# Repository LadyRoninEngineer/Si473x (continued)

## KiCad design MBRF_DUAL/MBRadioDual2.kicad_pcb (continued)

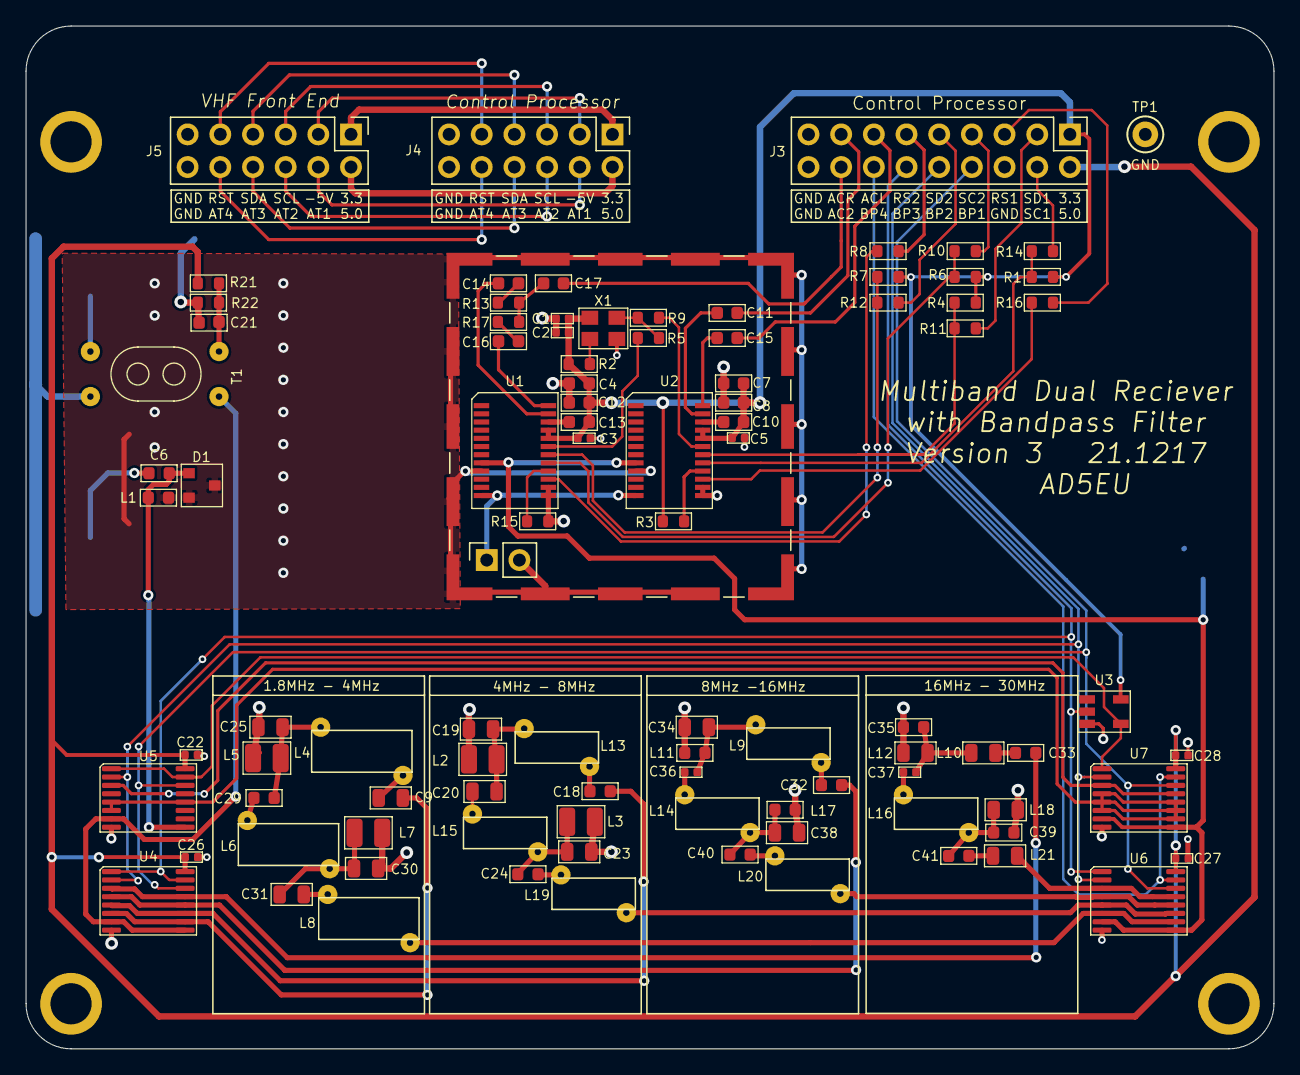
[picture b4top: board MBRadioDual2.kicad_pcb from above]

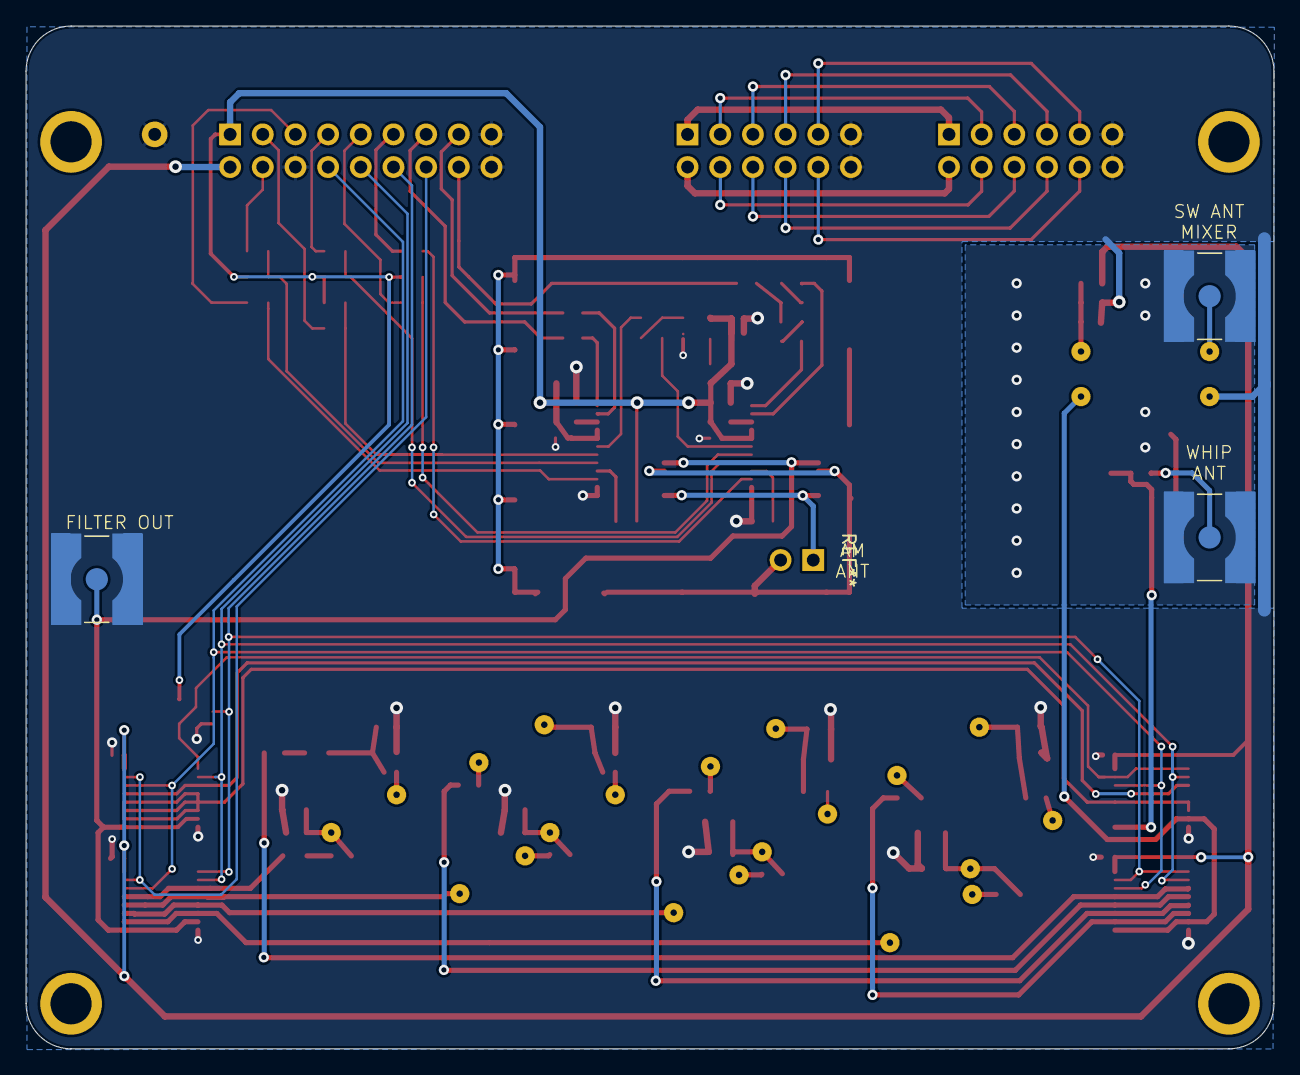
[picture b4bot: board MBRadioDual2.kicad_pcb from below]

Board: 2 copper layers, 97.0 x 79.5 mm, 99 parts (3 on the bottom side), 86 nets.

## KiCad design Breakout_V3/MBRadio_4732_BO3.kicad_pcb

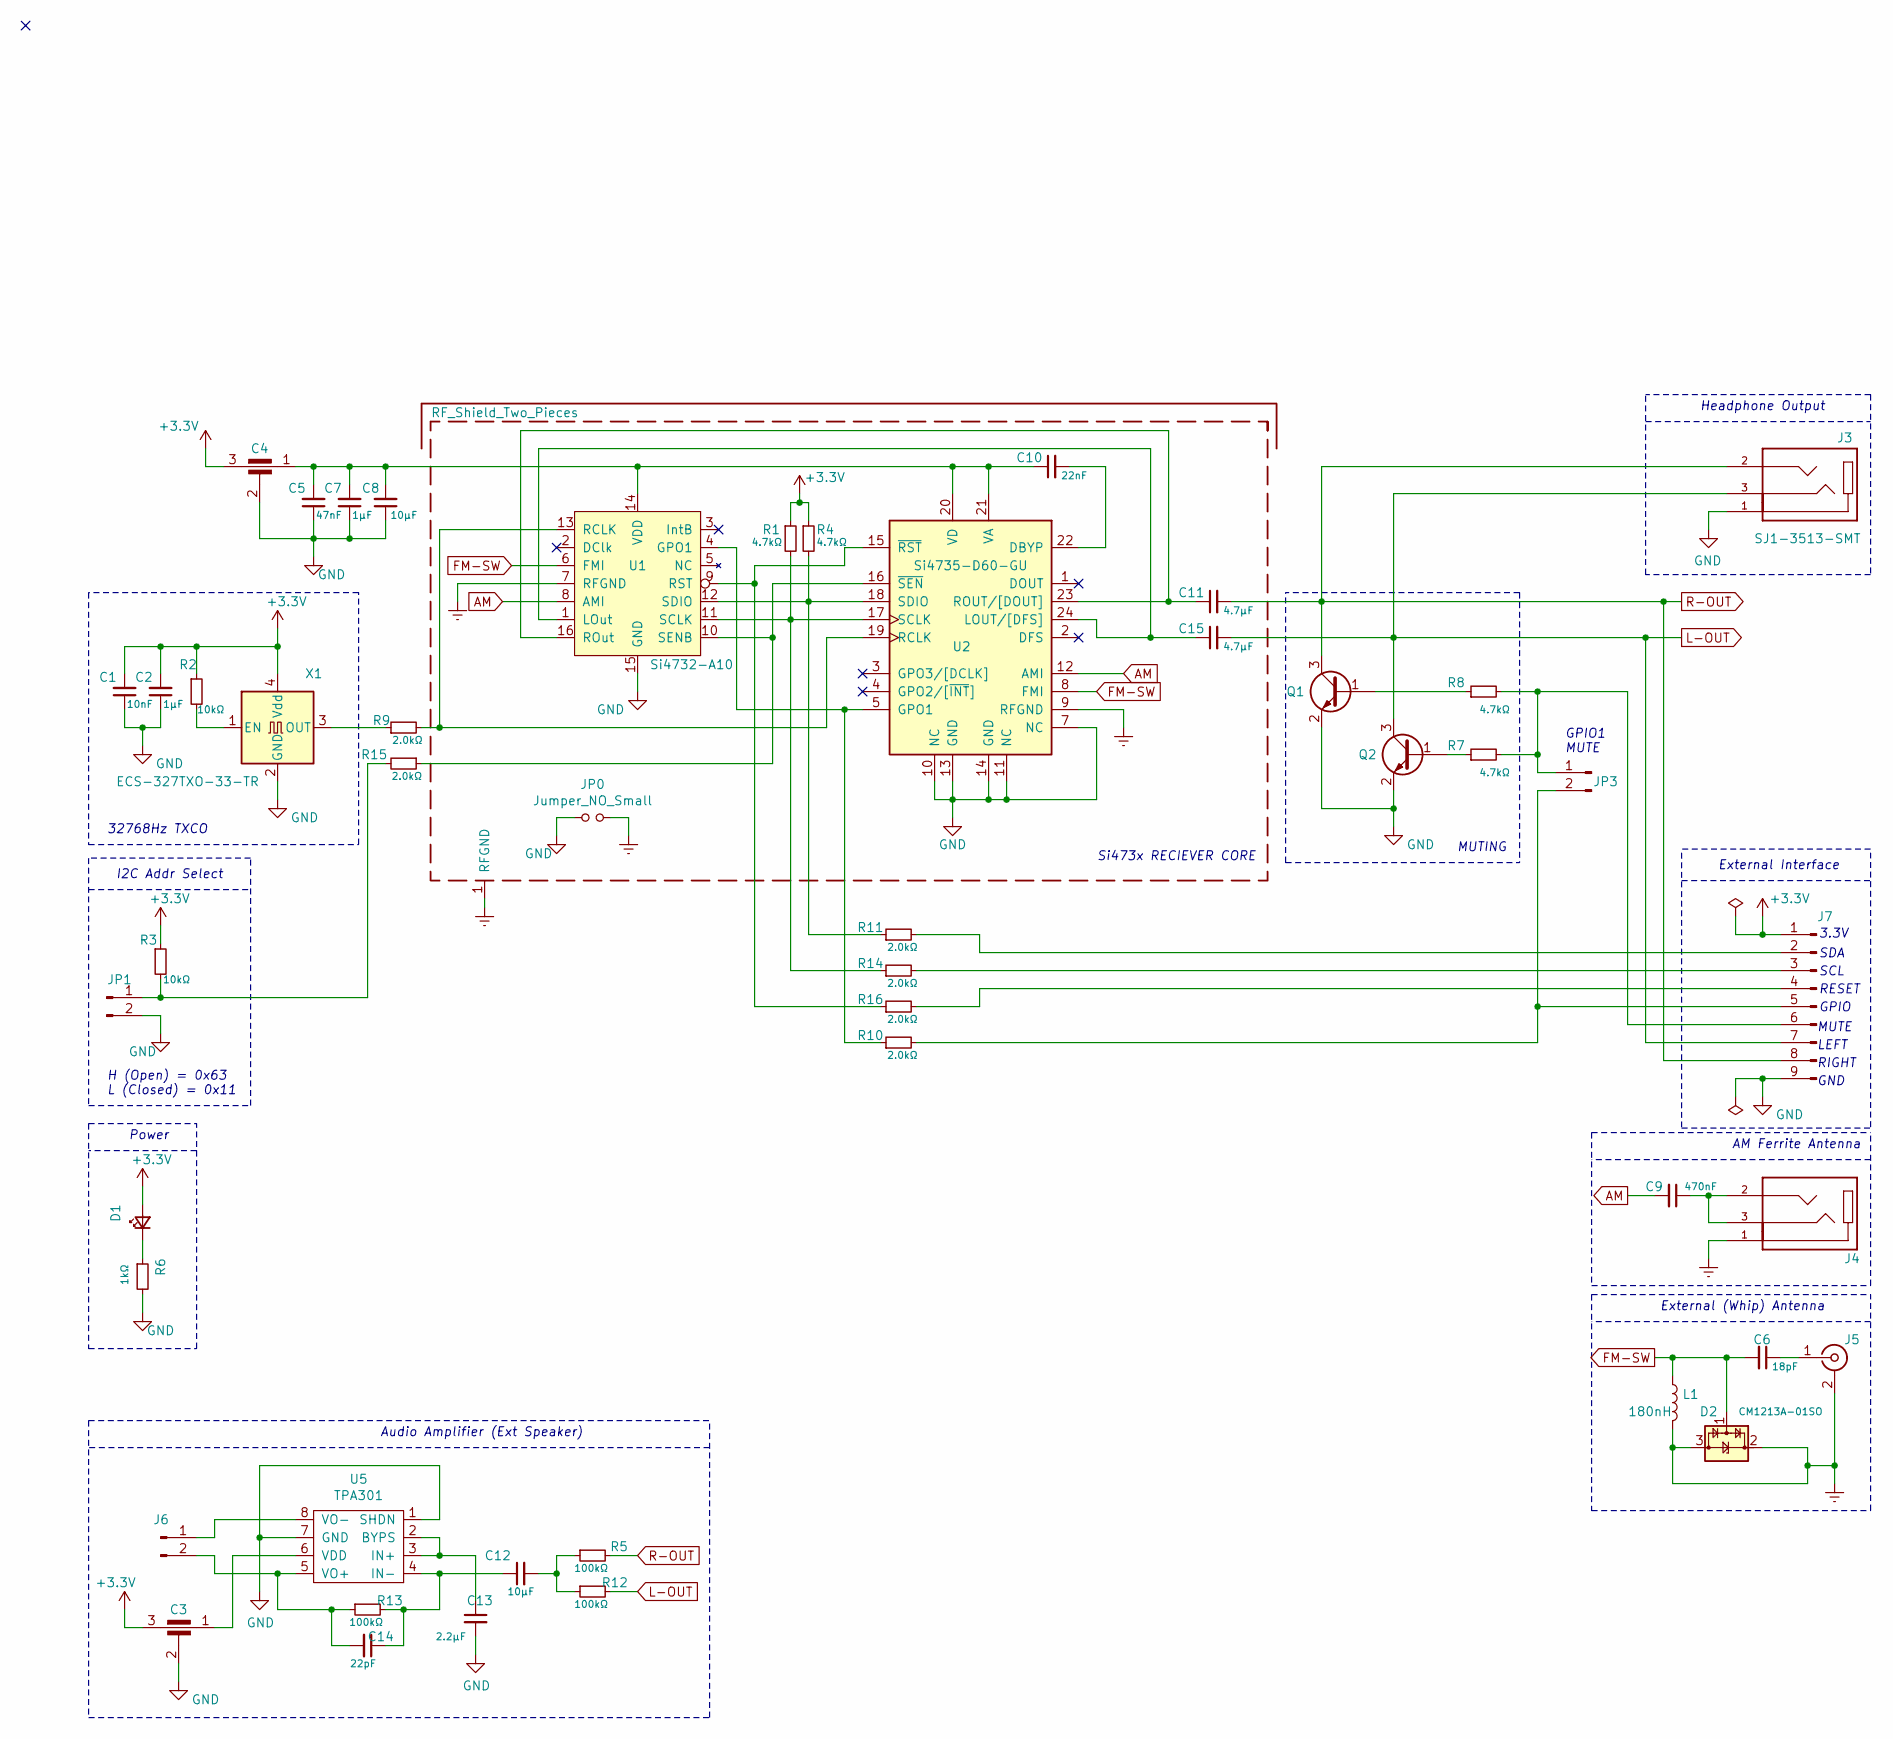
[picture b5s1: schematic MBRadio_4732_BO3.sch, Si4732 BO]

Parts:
C1: 10nF; C_0402_1005Metric
C2: 1µF; C_0402_1005Metric
C3, C4: EMI_Filter_C; NFM21PS106B0J3D
C5: 47nF; C_0402_1005Metric
C6: 18pF; C_0402_1005Metric
C7: 1µF; C_0603_1608Metric
C8, C12: 10µF; C_0603_1608Metric
C9: 470nF; C_0603_1608Metric
C10: 22nF; C_0603_1608Metric
C11, C15: 4.7µF; C_0603_1608Metric
C13: 2.2µF; C_0603_1608Metric
C14: 22pF; C_0402_1005Metric
D1: LED_Small; LED_0603_1608Metric_Castellated
D2: CM1213A-01SO; SOT-23
J3, J4: SJ1-3513-SMT; CUI_SJ1-3513-SMT
J5: Conn_01x01_Female; SMA_Molex_73251-1153_EdgeMount_Horizontal
J6: Conn_01x02_Male; TE_1776275-2
J7: Conn_01x09_Male; PinHeader_1x09_P2.54mm_Vertical
JP0: Jumper_NO_Small; SolderJumper-2_P1.3mm_Open_TrianglePad1.0x1.5mm
JP1, JP3: Conn_01x02_Male; PinHeader_1x02_P2.00mm_Vertical
L1: 180nH; L_0603_1608Metric
Q1, Q2: Q_NPN_BEC; SOT-23
R1, R4, R7, R8: 4.7kΩ; R_0603_1608Metric
R2, R3: 10kΩ; R_0603_1608Metric
R5, R12, R13: 100kΩ; R_0603_1608Metric
R6: 1kΩ; R_0603_1608Metric
R9, R10, R11, R14, R15, R16: 2.0kΩ; R_0603_1608Metric
SH1: RF_Shield_Two_Pieces; Laird_Technologies_BMI-S-203-F_26.21x26.21mm
U1: Si4732-A10; SOIC-16_3.9x9.9mm_P1.27mm
U2: Si4735-D60-GU; SSOP-24_3.9x8.7mm_P0.635mm
U5: TPA301; SOIC-8_3.9x4.9mm_P1.27mm
X1: ECS-327TXO-33-TR; Oscillator_SMD_Abracon_ASE-4Pin_3.2x2.5mm

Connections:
+3V3: C1.2, C2.2, C3.3, C4.3, D1.2 (A), J7.1, R1.1, R2.1, R3.1, R4.1, X1.4 (Vdd)
AM: C9.2, U1.8 (AMI), U2.12 (AMI)
Earth: D2.2 (VP), D2.3 (VN), J4.1, J5.2 (Ext), JP0.2, L1.2, SH1.1, U1.7 (RFGND), U2.9 (RFGND)
FM-SW: C6.2, D2.1 (CH1), L1.1, U1.6 (FMI), U2.8 (FMI)
GND: C1.1, C2.1, C3.2, C4.2, C5.1, C7.1, C8.1, C13.2, J3.1, J7.9, JP0.1, JP1.2, Q1.2 (E), Q2.2 (E), R6.2, U1.15 (GND), U2.7 (NC), U2.10 (NC), U2.11 (NC), U2.13 (GND), U2.14 (GND), U5.1 (SHDN), U5.7 (GND), X1.2 (GND)
L-OUT: C15.2, J3.3, J7.7, Q2.3 (C), R12.2
unnamed: C3.1, U5.6 (VDD)
unnamed: C6.1, J5.1 (In)
unnamed: C9.1, J4.2, J4.3
unnamed: C4.1, C5.2, C7.2, C8.2, C10.1, U1.14 (VDD), U2.20 (VD), U2.21 (VA)
unnamed: C10.2, U2.22 (DBYP)
unnamed: C11.1, U1.16 (ROut), U2.23 (ROUT/[DOUT])
unnamed: C12.1, C14.1, R13.2, U5.4 (IN-)
unnamed: C12.2, R5.1, R12.1
unnamed: C13.1, U5.2 (BYPS), U5.3 (IN+)
unnamed: C14.2, J6.2, R13.1, U5.5 (VO+)
unnamed: C15.1, U1.1 (LOut), U2.24 (LOUT/[DFS])
unnamed: D1.1 (K), R6.1
unnamed: J6.1, U5.8 (VO-)
unnamed: J7.2, R11.2
unnamed: J7.3, R14.2
unnamed: J7.4, R16.2
unnamed: J7.5, JP3.2, R10.2
unnamed: J7.6, JP3.1, R7.2, R8.2
unnamed: JP1.1, R3.2, R15.2
unnamed: Q1.1 (B), R8.1
unnamed: Q2.1 (B), R7.1
unnamed: R1.2, R14.1, U1.11 (SCLK), U2.17 (SCLK)
unnamed: R2.2, X1.1 (EN)
unnamed: R9.1, X1.3 (OUT)
unnamed: R9.2, U1.13 (RCLK), U2.19 (RCLK)
unnamed: R10.1, U1.4 (GPO1), U2.5 (GPO1)
unnamed: R4.2, R11.1, U1.12 (SDIO), U2.18 (SDIO)
unnamed: R15.1, U1.10 (SENB), U2.16 (~SEN)
unnamed: R16.1, U1.9 (RST), U2.15 (~RST)
R-OUT: C11.2, J3.2, J7.8, Q1.3 (C), R5.2

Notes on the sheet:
H (Open) = 0x63 L (Closed) = 0x11
Headphone Output
I2C Addr Select
Audio Amplifier (Ext Speaker)
External (Whip) Antenna
AM Ferrite Antenna
GPIO
RESET
External Interface
GND
3.3V
SDA
SCL
Si473x RECIEVER CORE
32768Hz TXCO
MUTING
GPIO1 MUTE
MUTE
RIGHT
LEFT
Power

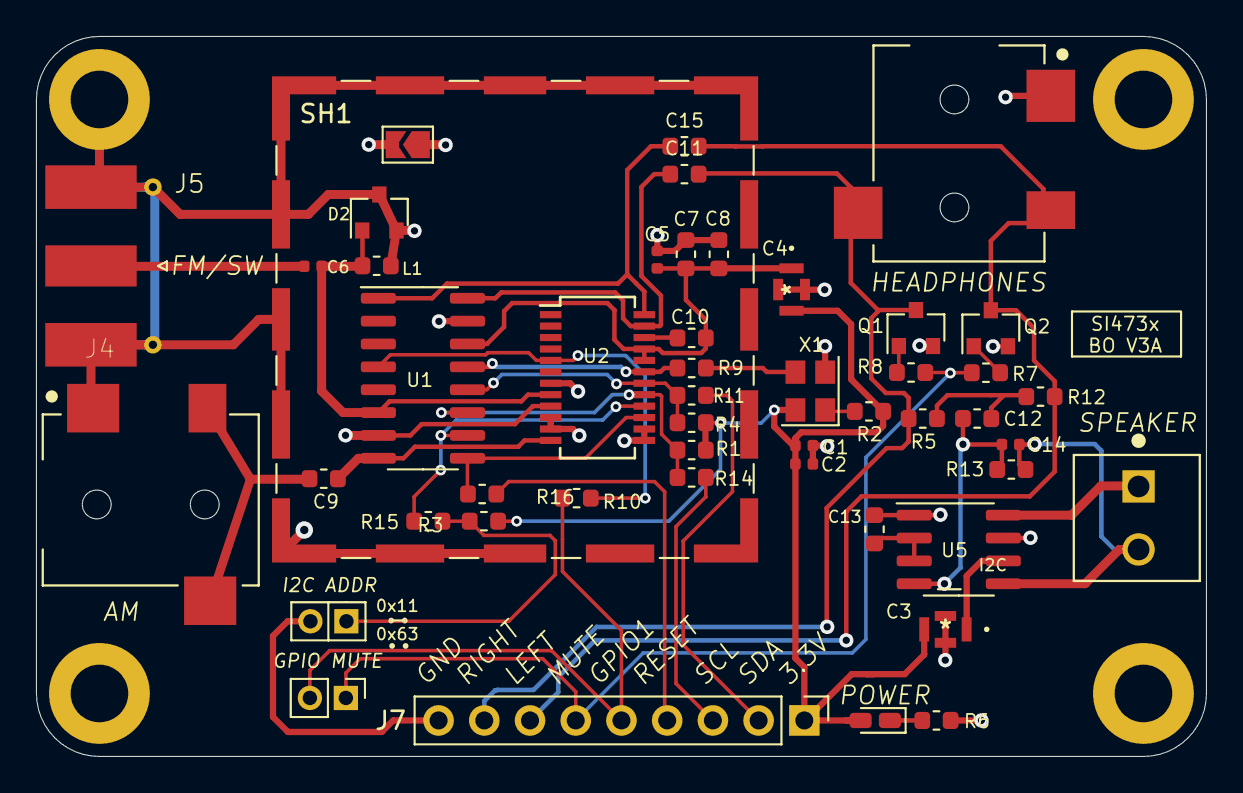
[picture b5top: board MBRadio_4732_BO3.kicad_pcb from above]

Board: 2 copper layers, 65.0 x 40.0 mm, 49 parts (0 on the bottom side), 36 nets.

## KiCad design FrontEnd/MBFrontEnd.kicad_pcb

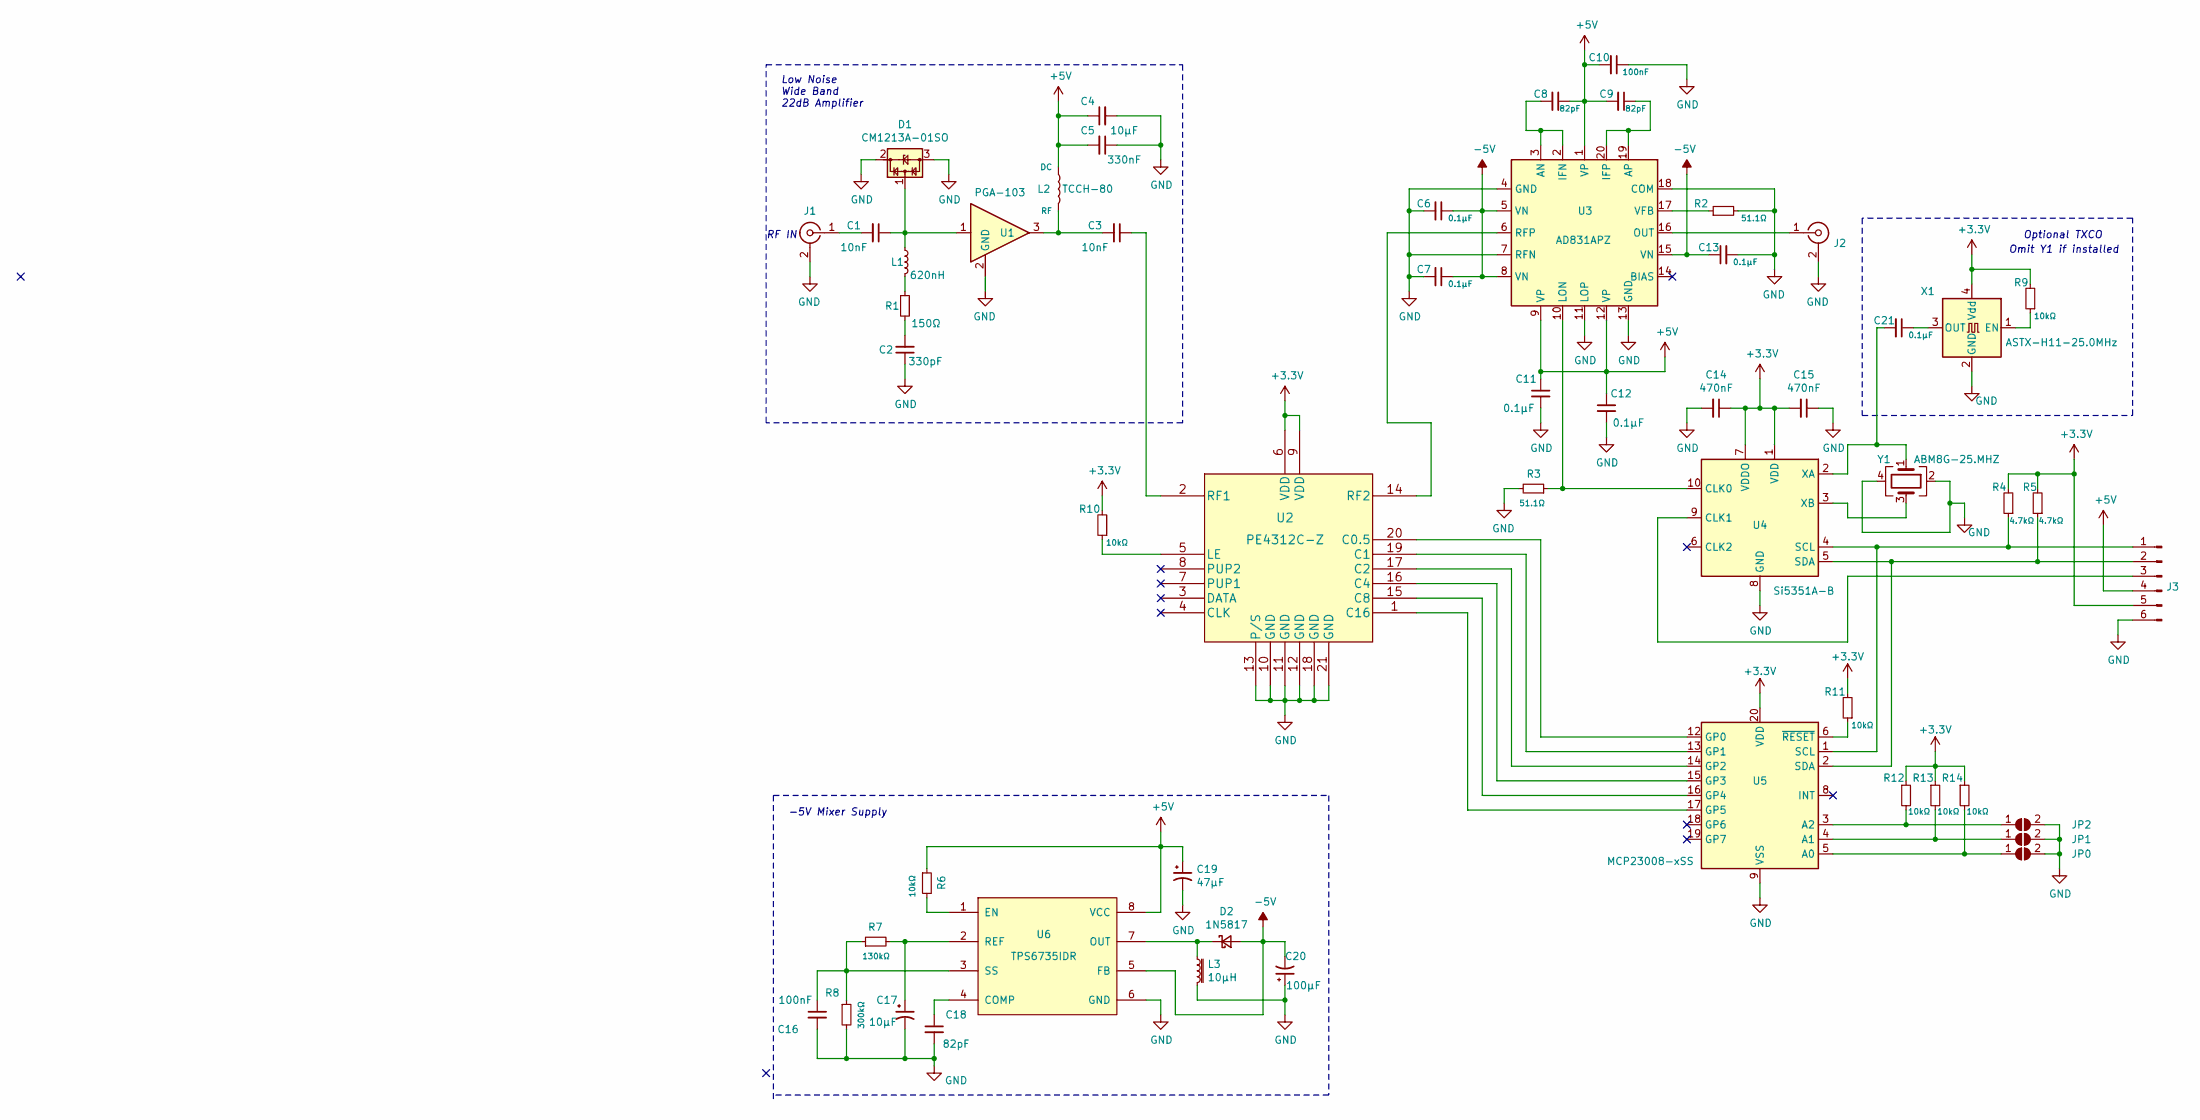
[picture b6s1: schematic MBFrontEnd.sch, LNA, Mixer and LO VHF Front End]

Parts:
C1, C3: 10nF; C_0805_2012Metric
C2: 330pF; C_0603_1608Metric
C4: 10µF; C_1206_3216Metric
C5: 330nF; C_0402_1005Metric
C6, C7, C11, C12, C13, C21: 0.1µF; C_0603_1608Metric
C8, C9, C18: 82pF; C_0402_1005Metric
C10: 100nF; C_0603_1608Metric
C14, C15: 470nF; C_0402_1005Metric
C16: 100nF; C_0402_1005Metric
C17: 10µF; CP_EIA-3528-21_Kemet-B
C19: 47µF; CP_EIA-7343-30_AVX-N
C20: 100µF; CP_EIA-7343-30_AVX-N
D1: CM1213A-01SO; SOT-23
D2: 1N5817; D_SOD-323
J1, J2: Conn_Coaxial; SMA_Molex_73251-1153_EdgeMount_Horizontal
J3: Conn_01x06_Male; PinHeader_1x06_P2.54mm_Horizontal
JP0, JP1, JP2: SolderJumper_2_Open; SolderJumper-2_P1.3mm_Open_TrianglePad1.0x1.5mm
L1: 620nH; L_1008_2520Metric
L2: TCCH-80; GU1604
L3: 10µH; CD54NP-220MC
R1: 150Ω; R_0603_1608Metric
R2, R3: 51.1Ω; R_0603_1608Metric
R4, R5: 4.7kΩ; R_0402_1005Metric
R6, R9, R10, R11, R12, R13, R14: 10kΩ; R_0402_1005Metric
R7: 130kΩ; R_0402_1005Metric
R8: 300kΩ; R_0402_1005Metric
U1: PGA-103; SOT-89-3
U2: PE4312C-Z; QFN-20-1EP_4x4mm_P0.5mm_EP2.6x2.6mm
U3: AD831APZ; PLCC-20
U4: Si5351A-B; MSOP-10_3x3mm_P0.5mm
U5: MCP23008-xSS; SSOP-20_5.3x7.2mm_P0.65mm
U6: TPS6735IDR; SOIC-8_3.9x4.9mm_P1.27mm
X1: ASTX-H11-25.0MHz; Oscillator_SMD_Abracon_ASE-4Pin_3.2x2.5mm
Y1: ABM8G-25.MHZ; Crystal_SMD_Abracon_ABM8G-4Pin_3.2x2.5mm

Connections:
+3V3: C14.1, C15.2, J3.5, R4.2, R5.2, R9.2, R10.2, R11.2, R12.1, R13.1, R14.1, U2.6 (VDD), U2.9 (VDD), U4.1 (VDD), U4.7 (VDDO), U5.20 (VDD), X1.4 (Vdd)
+5V: C4.1, C5.2, C8.1, C9.2, C10.2, C11.1, C12.1, C19.1, J3.4, L2.P$3 (DC), R6.1, U3.1 (VP), U3.9 (VP), U3.12 (VP), U6.8 (VCC)
-5V: C6.1, C7.1, C13.1, C20.2, D2.2 (A), U3.5 (VN), U3.8 (VN), U3.15 (VN), U6.5 (FB)
GND: C2.1, C4.2, C5.1, C6.2, C7.2, C10.1, C11.2, C12.2, C13.2, C14.2, C15.1, C16.2, C17.2, C18.2, C19.2, C20.1, D1.2 (VP), D1.3 (VN), J1.2 (Ext), J2.2 (Ext), J3.6, JP0.2 (B), JP1.2 (B), JP2.2 (B), L3.2, R2.2, R3.2, R8.2, U1.2 (GND), U2.10 (GND), U2.11 (GND), U2.12 (GND), U2.13 (P/S), U2.18 (GND), U2.21 (GND), U3.4 (GND), U3.7 (RFN), U3.11 (LOP), U3.13 (GND), U3.18 (COM), U4.8 (GND), U5.9 (VSS), U6.6 (GND), X1.2 (GND), Y1.2, Y1.4; also elsewhere on the board
unnamed: C1.1, D1.1 (CH1), L1.1, U1.1
unnamed: C1.2, J1.1 (In)
unnamed: C2.2, R1.2
unnamed: C3.1, U2.2 (RF1)
unnamed: C3.2, L2.P$1 (RF), U1.3
unnamed: C8.2, U3.2 (IFN), U3.3 (AN)
unnamed: C9.1, U3.19 (AP), U3.20 (IFP)
unnamed: C16.1, R7.1, R8.1, U6.3 (SS)
unnamed: C17.1, R7.2, U6.2 (REF)
unnamed: C18.1, U6.4 (COMP)
unnamed: C21.1, X1.3 (OUT)
unnamed: C21.2, U4.2 (XA), Y1.1
unnamed: D2.1 (K), L3.1, U6.7 (OUT)
unnamed: J2.1 (In), U3.16 (OUT)
unnamed: J3.1, R4.1, U4.4 (SCL), U5.1 (SCL)
unnamed: J3.2, R5.1, U4.5 (SDA), U5.2 (SDA)
unnamed: J3.3, U4.9 (CLK1)
unnamed 21: JP0.1 (A), R14.2, U5.5 (A0); also elsewhere on the board
unnamed 22: JP1.1 (A), R13.2, U5.4 (A1); also elsewhere on the board
unnamed 23: JP2.1 (A), R12.2, U5.3 (A2); also elsewhere on the board
unnamed: L1.2, R1.1
unnamed: R2.1, U3.17 (VFB)
unnamed: R3.1, U3.10 (LON), U4.10 (CLK0)
unnamed: R6.2, U6.1 (EN)
unnamed: R9.1, X1.1 (EN)
unnamed: R10.1, U2.5 (LE)
unnamed: R11.1, U5.6 (~RESET)
unnamed: U2.1 (C16), U5.17 (GP5)
unnamed: U2.14 (RF2), U3.6 (RFP)
unnamed: U2.15 (C8), U5.16 (GP4)
unnamed: U2.16 (C4), U5.15 (GP3)
unnamed: U2.17 (C2), U5.14 (GP2)
unnamed: U2.19 (C1), U5.13 (GP1)
unnamed: U2.20 (C0.5), U5.12 (GP0)
unnamed: U4.3 (XB), Y1.3

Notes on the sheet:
-5V Mixer Supply
RF IN
Low Noise Wide Band 22dB Amplifier
Optional TXCO
Omit Y1 if installed

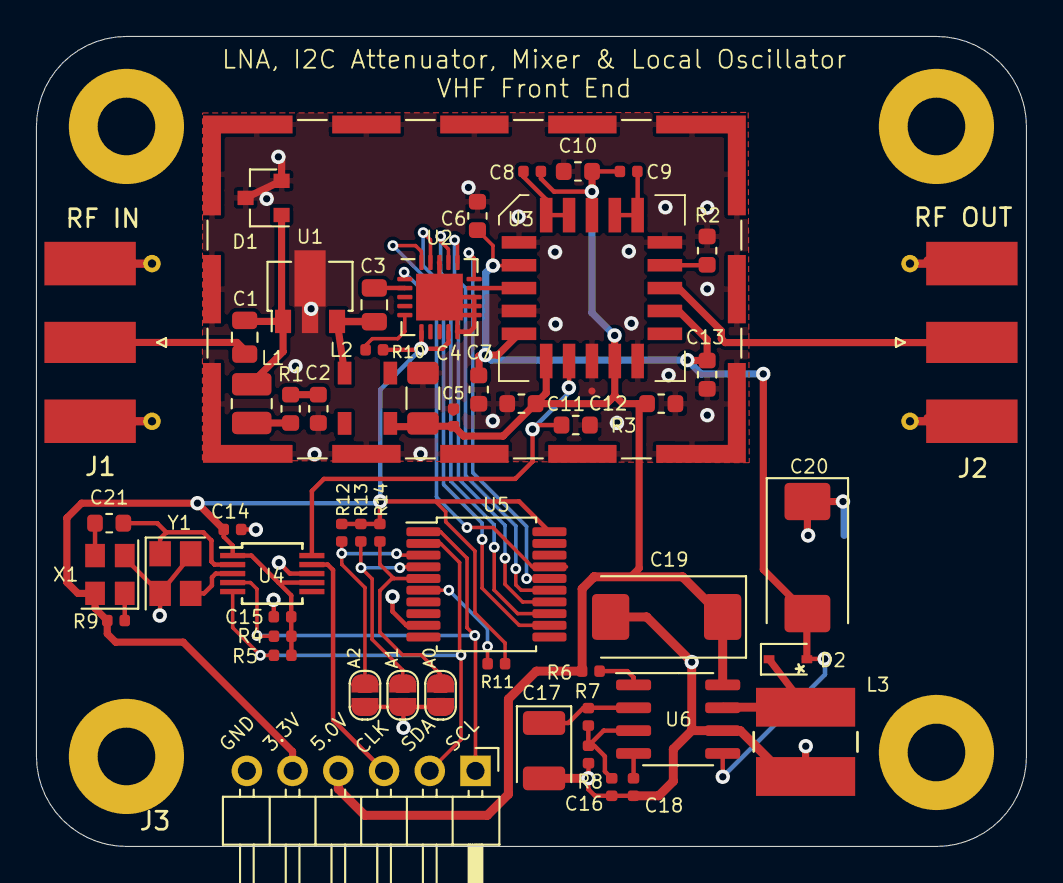
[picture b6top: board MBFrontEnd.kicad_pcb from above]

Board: 2 copper layers, 55.0 x 45.0 mm, 54 parts (0 on the bottom side), 39 nets.

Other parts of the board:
A0, A1, A2: SolderJumper-2_P1.3mm_Open_RoundedPad1.0x1.5mm

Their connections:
GND: A0.2, A1.2, A2.2; also elsewhere on the board
unnamed 21: A0.1; also elsewhere on the board
unnamed 22: A1.1; also elsewhere on the board
unnamed 23: A2.1; also elsewhere on the board

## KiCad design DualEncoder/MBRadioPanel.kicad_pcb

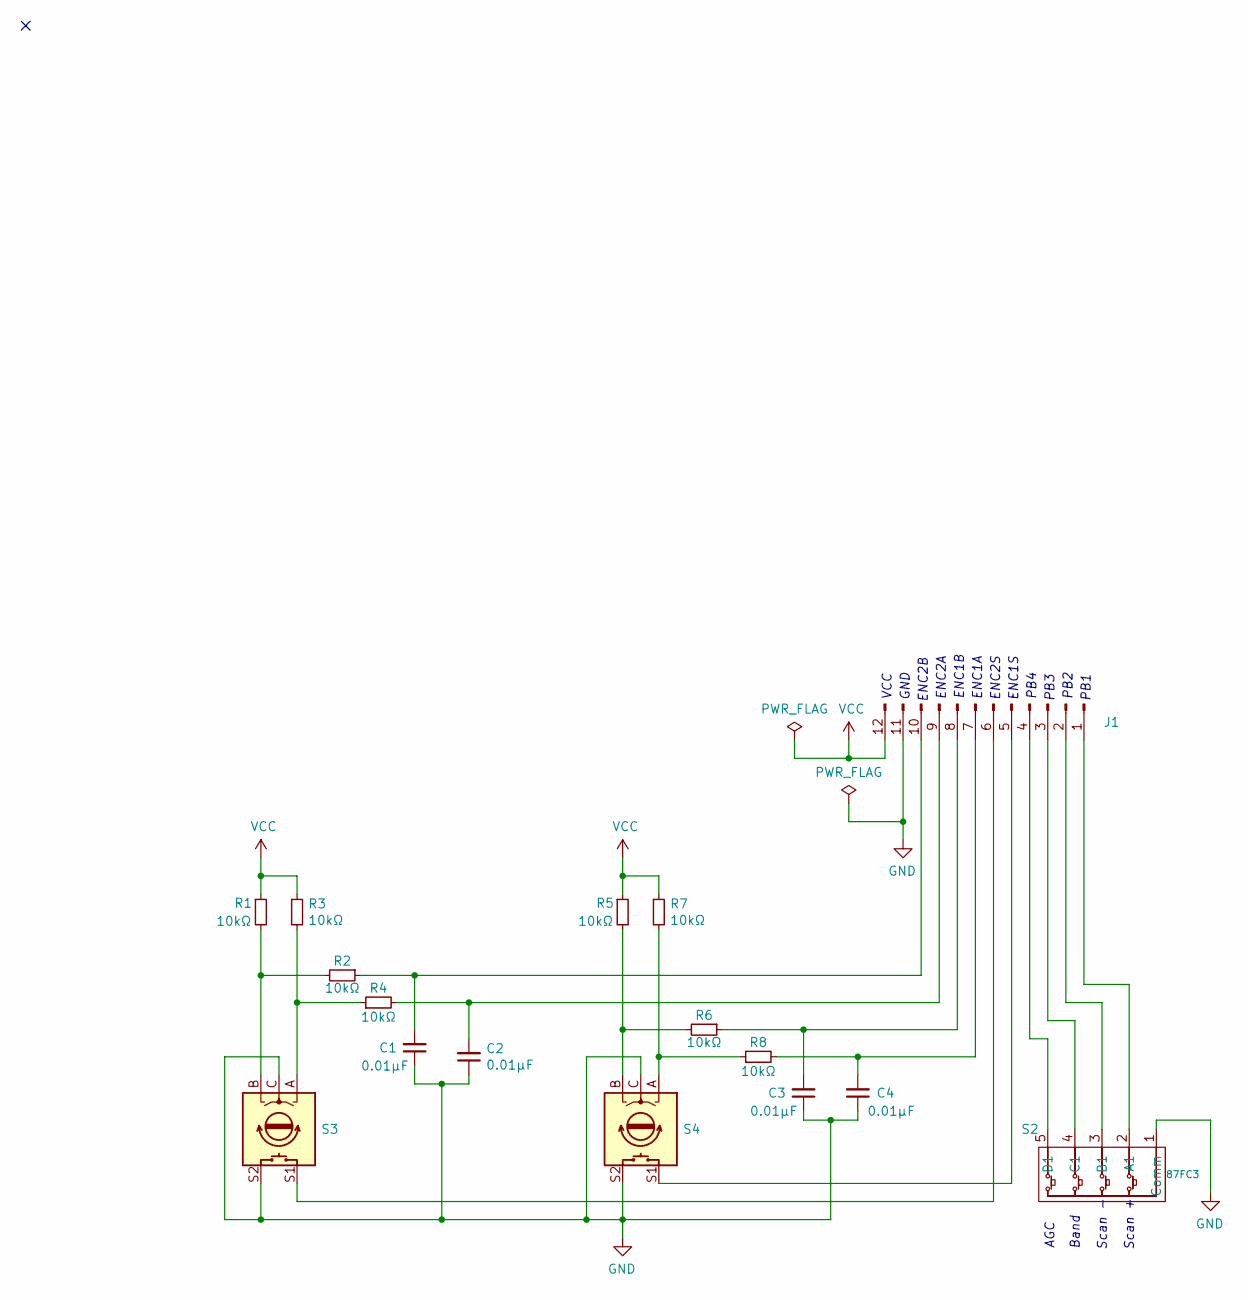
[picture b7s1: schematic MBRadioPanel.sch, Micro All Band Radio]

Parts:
C1, C2, C3, C4: 0.01µF; C_0402_1005Metric
J1: Conn_01x12_Male; PinHeader_1x12_P2.54mm_Vertical
R1, R2, R3, R4, R5, R6, R7, R8: 10kΩ; R_0402_1005Metric
S2: 87FC3
S3, S4: Rotary_Encoder_Switch; RotaryEncoder_Alps_EC11E-Switch_Vertical_H20mm

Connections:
GND: C1.1, C2.1, C3.1, C4.1, J1.11, S2.1 (Comm), S3.C, S3.S2, S4.C, S4.S2
unnamed: C1.2, J1.10, R2.1
unnamed: C2.2, J1.9, R4.2
unnamed: C3.2, J1.8, R6.1
unnamed: C4.2, J1.7, R8.2
unnamed: J1.1, S2.2 (A1)
unnamed: J1.2, S2.3 (B1)
unnamed: J1.3, S2.4 (C1)
unnamed: J1.4, S2.5 (D1)
unnamed: J1.5, S4.S1
unnamed: J1.6, S3.S1
unnamed: R1.2, R2.2, S3.B
unnamed: R3.2, R4.1, S3.A
unnamed: R5.2, R6.2, S4.B
unnamed: R7.2, R8.1, S4.A
VCC: J1.12, R1.1, R3.1, R5.1, R7.1

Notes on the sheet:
AGC
Band
Scan -
Scan +
ENC2B
ENC2A
ENC1B
ENC1A
ENC2S
ENC1S
PB4
PB3
GND
PB2
PB1
VCC

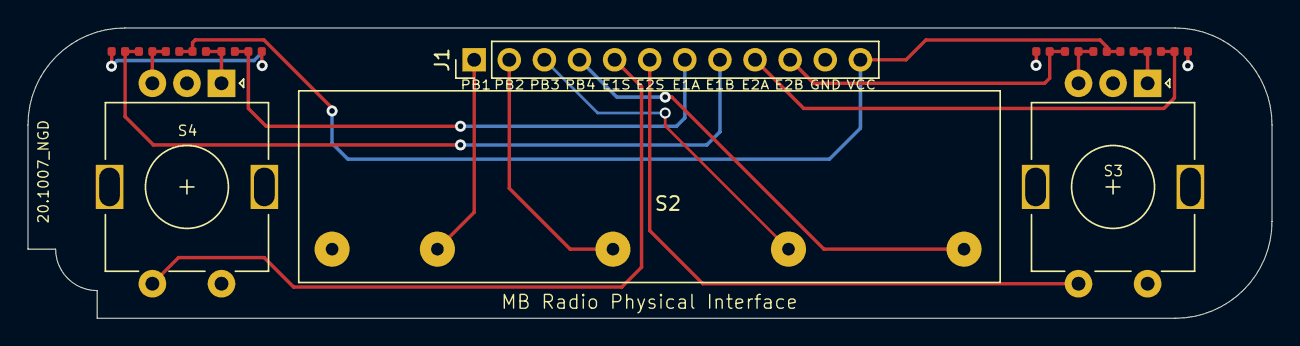
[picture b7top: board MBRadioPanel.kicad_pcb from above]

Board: 2 copper layers, 90.0 x 21.0 mm, 16 parts (0 on the bottom side), 16 nets.

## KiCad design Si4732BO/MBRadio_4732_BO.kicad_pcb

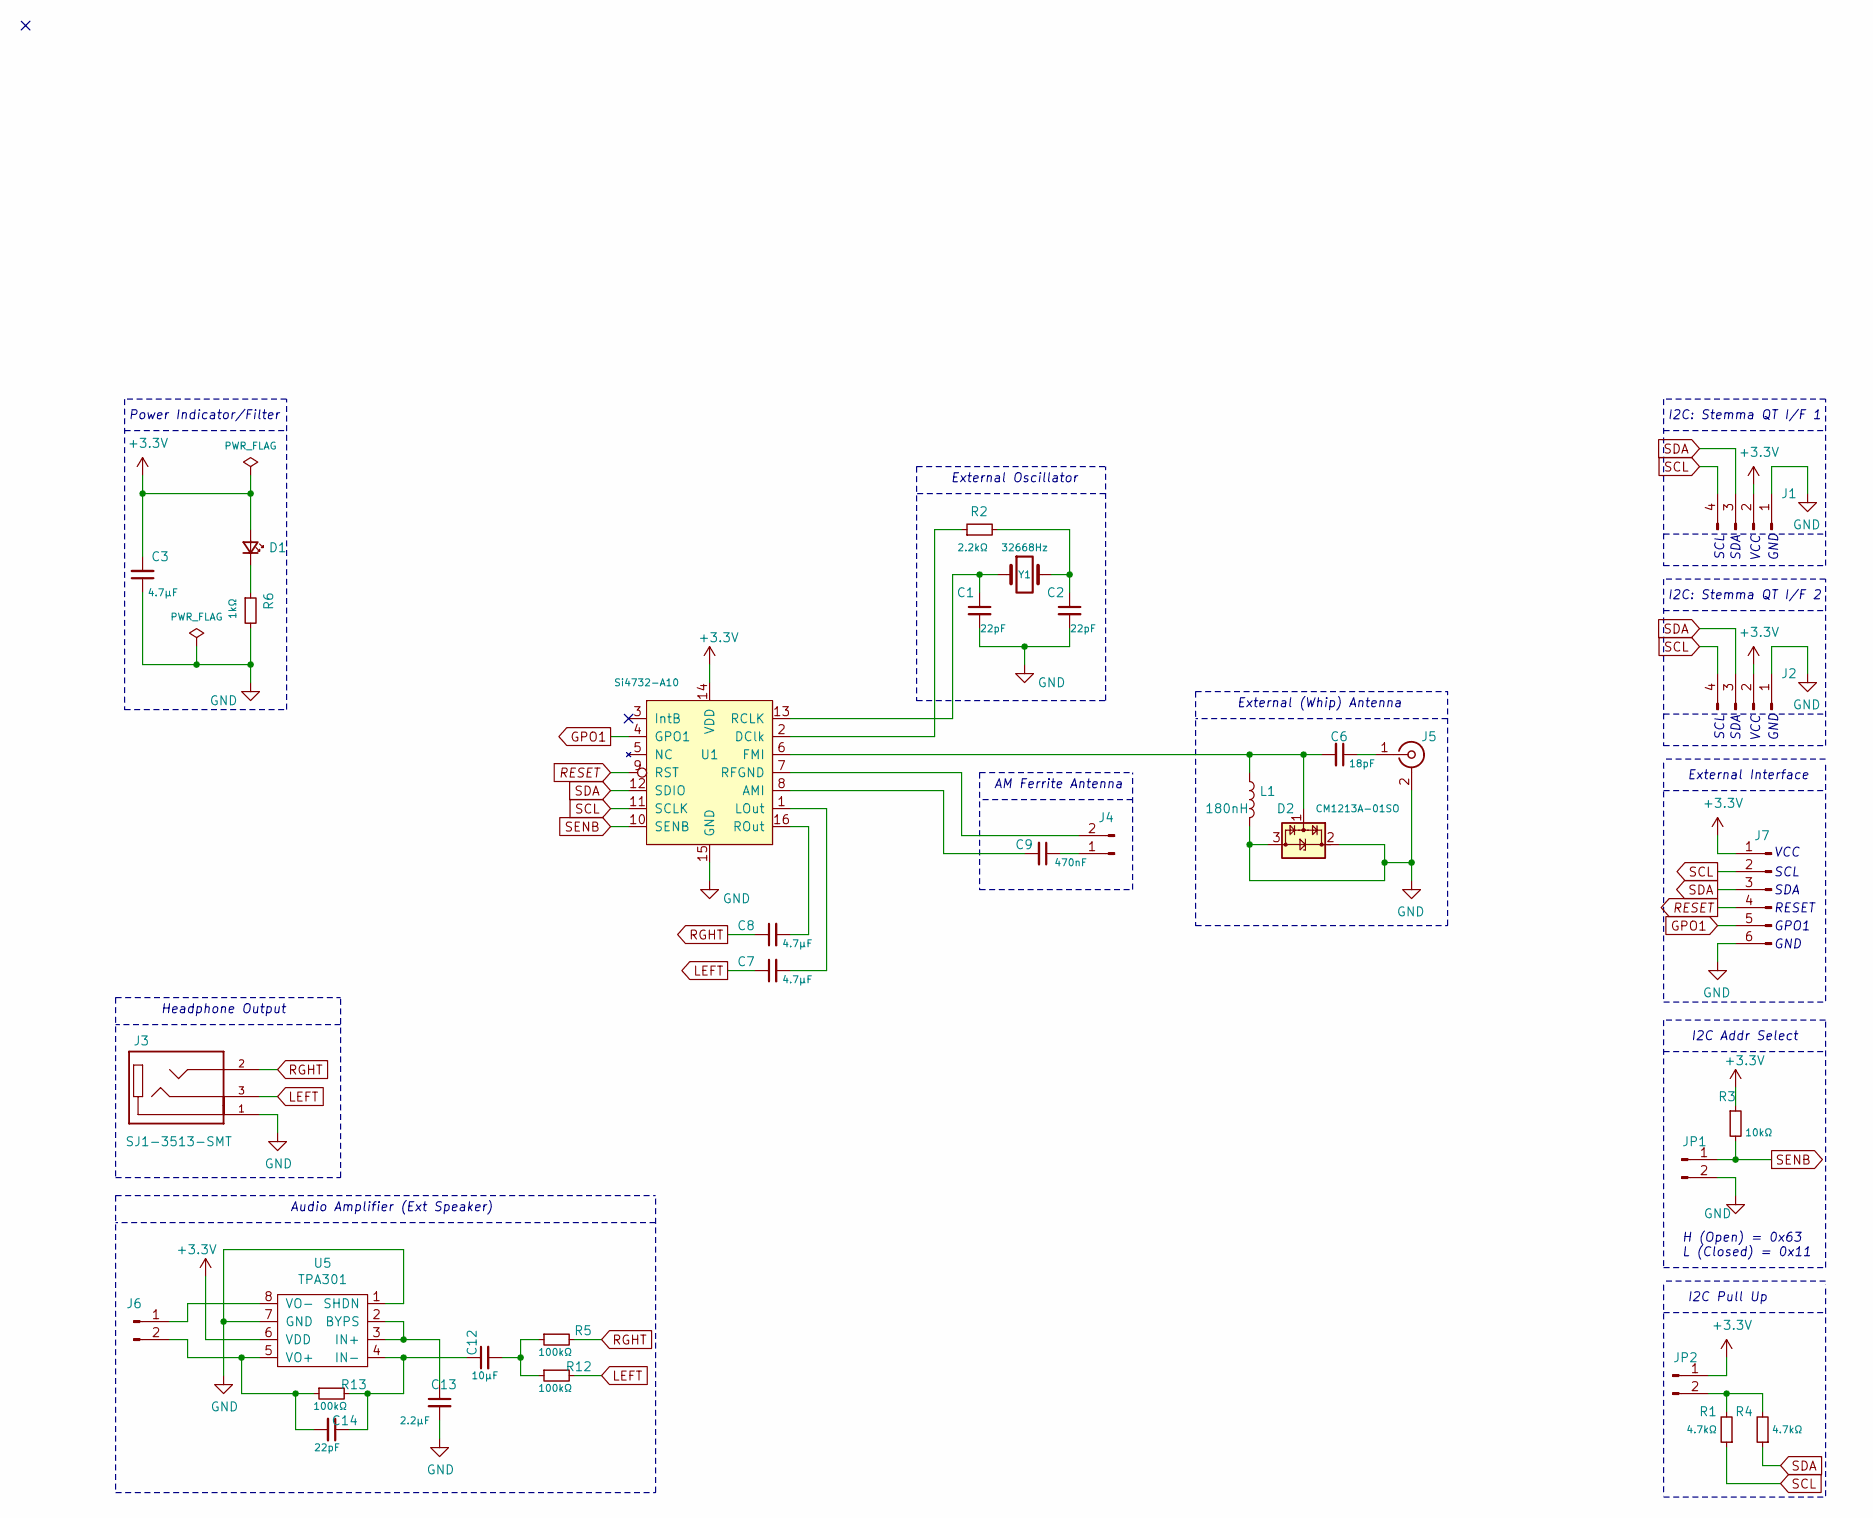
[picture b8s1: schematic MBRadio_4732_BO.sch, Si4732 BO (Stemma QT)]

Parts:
C1, C2, C14: 22pF; C_0402_1005Metric
C3, C7, C8: 4.7µF; C_0603_1608Metric
C6: 18pF; C_0402_1005Metric
C9: 470nF; C_0402_1005Metric
C12: 10µF; C_0603_1608Metric
C13: 2.2µF; C_0402_1005Metric
D1: LED_Small; LED_0402_1005Metric
D2: CM1213A-01SO; SOT-23
J1, J2: Conn_01x04_Male; JST_SH_SM04B-SRSS-TB_1x04-1MP_P1.00mm_Horizontal
J3: SJ1-3513-SMT; CUI_SJ1-3513-SMT
J4: Conn_01x02_Male; PinHeader_1x02_P2.00mm_Vertical
J5: Conn_01x01_Female; U.FL_Hirose_U.FL-R-SMT-1_Vertical
J6: Conn_01x02_Male; PinHeader_1x02_P2.54mm_Vertical
J7: Conn_01x06_Male; PinHeader_1x06_P2.54mm_Vertical
JP1, JP2: Conn_01x02_Male; PinHeader_1x02_P2.00mm_Vertical
L1: 180nH; L_0603_1608Metric
R1, R4: 4.7kΩ; R_0402_1005Metric
R2: 2.2kΩ; R_0402_1005Metric
R3: 10kΩ; R_0402_1005Metric
R5, R12, R13: 100kΩ; R_0402_1005Metric
R6: 1kΩ; R_0402_1005Metric
U1: Si4732-A10; SOIC-16_3.9x9.9mm_P1.27mm
U5: TPA301; SOIC-8_3.9x4.9mm_P1.27mm
Y1: 32668Hz; Crystal_SMD_MicroCrystal_CC7V-T1A-2Pin_3.2x1.5mm

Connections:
+3V3: C3.2, D1.2 (A), J1.2, J2.2, J7.1, JP2.1, R3.1, U1.14 (VDD), U5.6 (VDD)
GND: C1.2, C2.2, C3.1, C13.2, D2.2 (VP), D2.3 (VN), J1.1, J2.1, J3.1, J5.2 (Ext), J7.6, JP1.2, L1.2, R6.2, U1.15 (GND), U5.1 (SHDN), U5.7 (GND)
GPO1: J7.5, U1.4 (GPO1)
LEFT: C7.1, J3.3, R12.2
unnamed: C1.1, U1.13 (RCLK), Y1.1
unnamed: C2.1, R2.2, Y1.2
unnamed: C6.1, J5.1 (In)
unnamed: C6.2, D2.1 (CH1), L1.1, U1.6 (FMI)
unnamed: C7.2, U1.1 (LOut)
unnamed: C8.2, U1.16 (ROut)
unnamed: C9.1, J4.1
unnamed: C9.2, U1.8 (AMI)
unnamed: C12.1, C14.1, R13.2, U5.4 (IN-)
unnamed: C12.2, R5.1, R12.1
unnamed: C13.1, U5.2 (BYPS), U5.3 (IN+)
unnamed: C14.2, J6.2, R13.1, U5.5 (VO+)
unnamed: D1.1 (K), R6.1
unnamed: J4.2, U1.7 (RFGND)
unnamed: J6.1, U5.8 (VO-)
unnamed: JP2.2, R1.2, R4.2
unnamed: R2.1, U1.2 (DClk)
RESET: J7.4, U1.9 (RST)
RGHT: C8.1, J3.2, R5.2
SCL: J1.4, J2.4, J7.2, R1.1, U1.11 (SCLK)
SDA: J1.3, J2.3, J7.3, R4.1, U1.12 (SDIO)
SENB: JP1.1, R3.2, U1.10 (SENB)

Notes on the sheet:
SDA
SCL
VCC
GND
H (Open) = 0x63 L (Closed) = 0x11
Headphone Output
I2C: Stemma QT I/F 1
External Interface
RESET
GPO1
I2C: Stemma QT I/F 2
I2C Pull Up
Power Indicator/Filter
I2C Addr Select
Audio Amplifier (Ext Speaker)
External (Whip) Antenna
External Oscillator
AM Ferrite Antenna

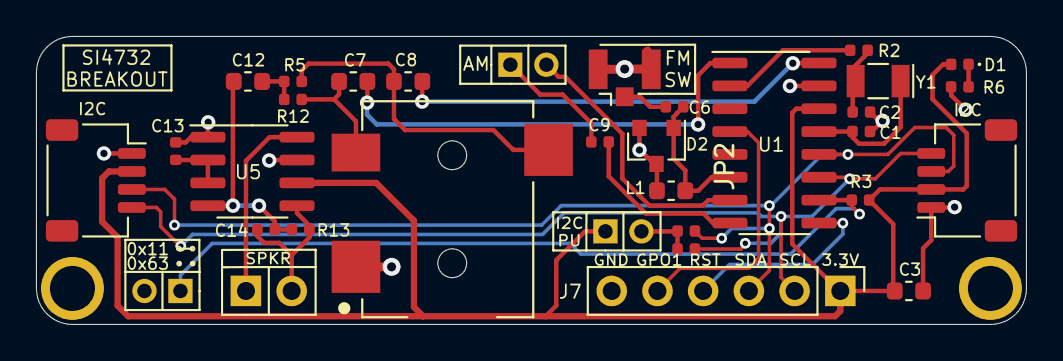
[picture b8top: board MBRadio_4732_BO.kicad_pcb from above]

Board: 2 copper layers, 55.0 x 16.0 mm, 33 parts (0 on the bottom side), 26 nets.

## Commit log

2020-11-09 Create Gerbers
2021-02-23 Create Front End
2021-02-23 Create null
2022-02-08 Multiband Radio V4 Schematics
2022-02-10 MBR Bill of Materials
